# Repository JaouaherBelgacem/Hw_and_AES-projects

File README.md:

******Hw and AES projects TEAM-01 ******

This folder is for Prof Ali Hayek projects of Hardware engineering and Advanced Embedded System's projects

---------Team Members AES---------
* Jaouaher Belgacem
* Jasmeet Singh

---------Team Members HWE---------
* Jaouaher Belgacem
* Jasmeet Singh
* Evrard Leuteu Feukeu

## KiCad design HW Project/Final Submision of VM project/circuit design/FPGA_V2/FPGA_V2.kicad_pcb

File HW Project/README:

************ The Project Submission ************
* The draft submission of the documentation, vhdl and fpga implementations are included in the Vending machine project folder.

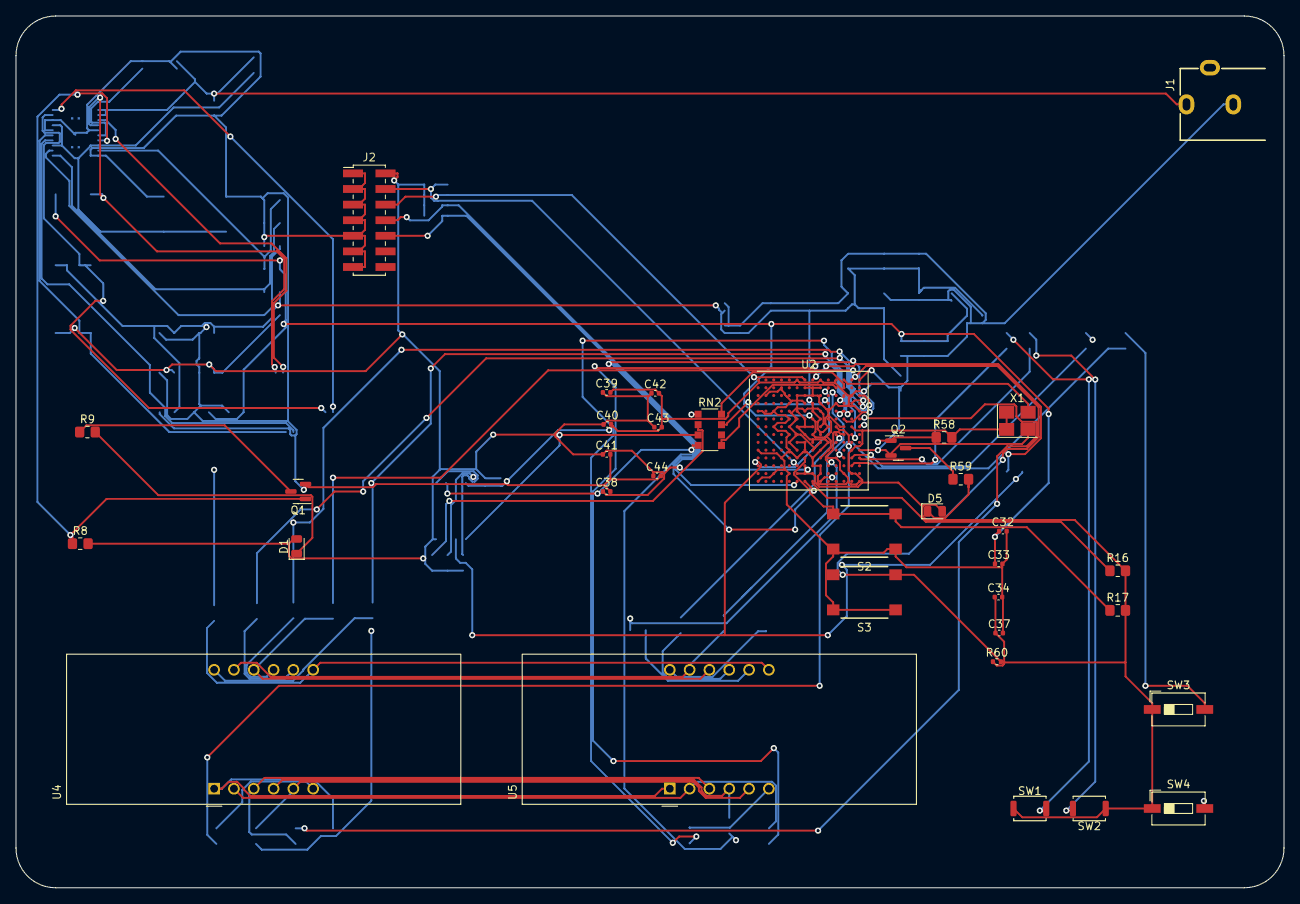
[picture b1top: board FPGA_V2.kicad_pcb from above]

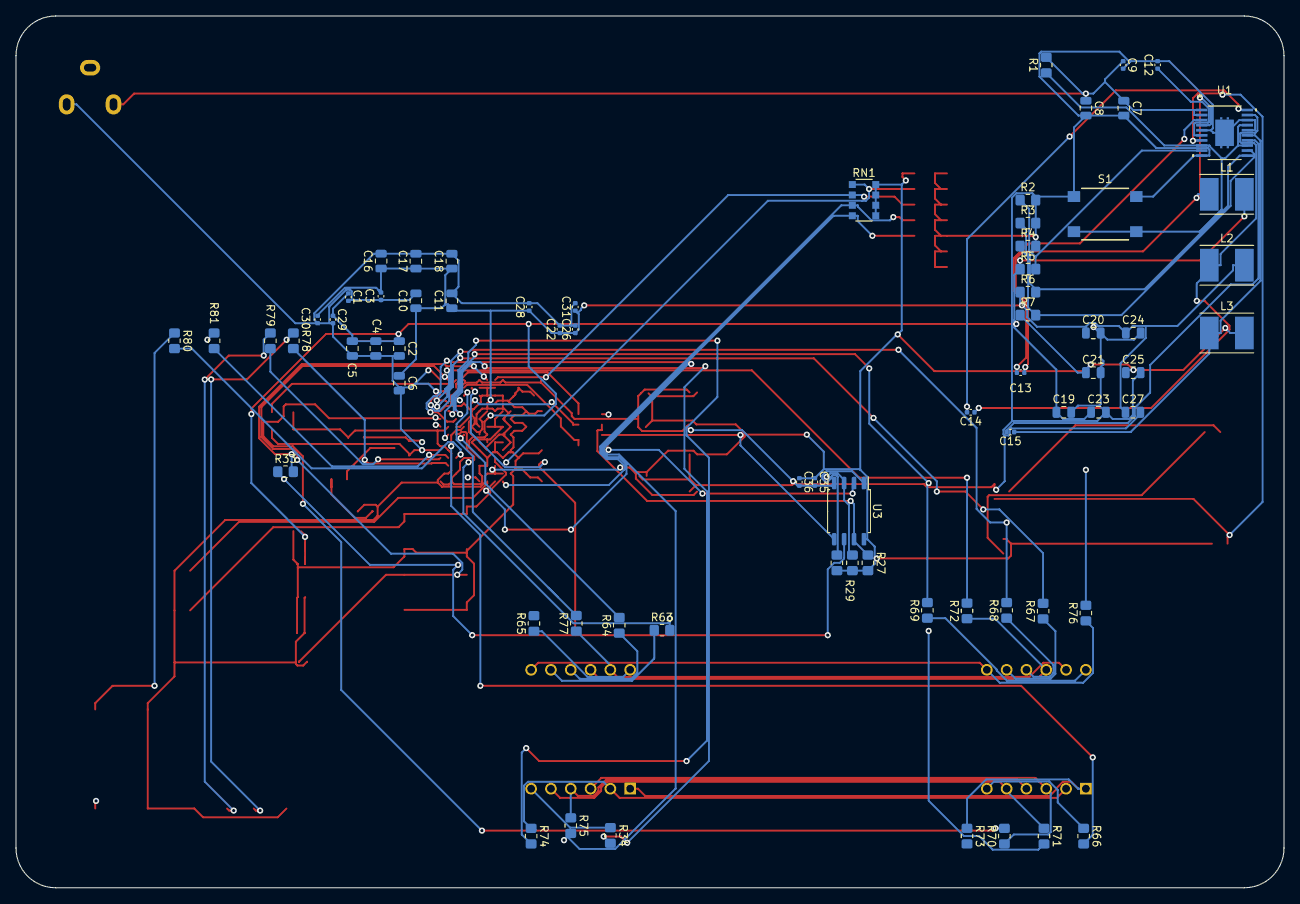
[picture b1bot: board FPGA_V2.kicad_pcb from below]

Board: 2 copper layers, 162.6 x 111.8 mm, 106 parts (71 on the bottom side), 81 nets.

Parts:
C1, C3, C22, C26, C28, C29, C38, C39: 4.7 uF; C_0402_1005Metric
C2, C4, C5, C6, C10, C11, C16, C17, C18: 0.47 uF; C_0805_2012Metric
C7, C8: 10 uF; C_0805_2012Metric
C9, C13, C14, C15, C32, C33, C35, C37: 0.1 uF; C_0402_1005Metric
C12, C36: 1 uF; C_0402_1005Metric
C19, C20, C21, C23, C24, C25, C27: 22 uF; C_0805_2012Metric
C30, C34, C44: 47 uF; C_0402_1005Metric
C31: 100 uF; C_0402_1005Metric
C40, C41, C42, C43: 0.47 uF; C_0402_1005Metric
D1: POWER_GOOD; LED_0805_2012Metric
D5: FPGA_DONE; LED_0805_2012Metric
J1: Barrel_Jack_Switch; PJ_102B
J2: XILINX_JTAG; PinHeader_2x07_P2.00mm_Vertical_SMD
L1, L2, L3: 2.2 uH; L_Taiyo-Yuden_NR-50xx_HandSoldering
Q1, Q2: DMN2020L; SOT-23
R1, R8: 100K; R_0805_2012Metric_Pad1.20x1.40mm_HandSolder
R2, R3, R4: 2.2K; R_0805_2012Metric_Pad1.20x1.40mm_HandSolder
R5: 3.0K; R_0805_2012Metric_Pad1.20x1.40mm_HandSolder
R6, R9, R59: 680; R_0805_2012Metric_Pad1.20x1.40mm_HandSolder
R7: 7.36K; R_0805_2012Metric_Pad1.20x1.40mm_HandSolder
R16, R17, R27, R28, R29: 4.75K; R_0805_2012Metric_Pad1.20x1.40mm_HandSolder
R33: 49.9; R_0805_2012Metric_Pad1.20x1.40mm_HandSolder
R34, R58, R63, R64, R65, R66, R67, R68, R69, R70, R71, R72, R73, R74, R75, R76, R77, R78, R79, R80, R81: 330; R_0805_2012Metric_Pad1.20x1.40mm_HandSolder
R60: 4.75K; R_0402_1005Metric
RN1: 10K; R_Array_Convex_4x1206
RN2: 49.9; R_Array_Convex_4x1206
S1, S2, S3: B3FS_1010P
SW1, SW2: SW_Push; SW_Push_SPST_NO_Alps_SKRK
SW3, SW4: SW_DIP_x01; SW_DIP_SPSTx01_Slide_6.7x4.1mm_W6.73mm_P2.54mm_LowProfile_J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
U1: TPS65581; PWP20_2P4X3P4_TEX
U2: XC7S50-FTGB196; Xilinx_FTGB196
U3: QSPI_Flash_SOIC8; SOIC-8_5.275x5.275mm_P1.27mm
U4, U5: CA56-12CGKWA
X1: DSC61XX; Oscillator_SMD_Abracon_ASE-4Pin_3.2x2.5mm_HandSoldering

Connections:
+1V0: C3.1, C6.1, C10.1, C11.1, C16.1, C17.1, C18.1, C20.1, C22.1, C24.1, C26.1, C27.1, C28.1, C30.1, C31.1, L2.2, R6.1, U2.D6 (VCCINT), U2.D8 (VCCINT), U2.E5 (VCCBRAM), U2.E7 (VCCINT), U2.E9 (VCCINT), U2.F6 (VCCINT), U2.G5 (VCCBRAM), U2.G9 (VCCINT), U2.H6 (VCCINT), U2.J5 (VCCBRAM), U2.J9 (VCCINT), U2.K6 (VCCINT), U2.K8 (VCCINT)
+1V8: C1.1, C2.1, C4.1, C5.1, C19.1, C23.1, C29.1, C32.1, C33.1, L1.2, R5.1, U2.F8 (VCCADC_0), U2.F10 (VCCAUX), U2.H8 (VREFP_0), U2.H10 (VCCAUX), U2.K10 (VCCAUX), U2.L9 (VCCAUX)
+3V3: C21.1, C25.1, C34.1, C35.1, C36.1, C37.1, C38.1, C39.1, C40.1, C41.1, C42.1, C43.1, C44.1, D1.2 (A), D5.2 (A), J2.2 (VREF), L3.2, R7.1, R8.2, R16.2, R17.2, R27.2, R28.2, R29.2, R58.2, R60.1, RN1.5 (R4.2), RN1.6 (R3.2), RN1.7 (R2.2), RN1.8 (R1.2), SW1.1, SW2.1, SW3.1, SW4.1, U2.G13 (VCCO_14), U2.K13 (VCCO_14), U2.M7 (M0_0), U2.N6 (VCCO_0), U2.N7 (CFGBVS_0), U2.N8 (VCCO_0), U2.N13 (VCCO_14), U3.8 (VCC), X1.1 (OE), X1.4 (VCC)
+12V: C7.1, C8.1, C9.1, J1.1, R1.2, U1.1 (VIN), U1.2 (VIN)
/IO/AN0: R69.1, U4.12 (CA1)
/IO/AN1: R68.1, U4.9 (CA2)
/IO/AN2: R67.1, U4.8 (CA3)
/IO/AN3: R66.1, U4.6 (CA4)
/IO/AN4: R65.1, U5.12 (CA1)
/IO/AN5: R64.1, U5.9 (CA2)
/IO/AN6: R63.1, U5.8 (CA3)
/IO/AN7: R34.1, U5.6 (CA4)
/IO/DA: R77.1, U4.11 (a), U5.11 (a)
/IO/DB: R76.1, U4.7 (b), U5.7 (b)
/IO/DC: R75.1, U4.4 (c), U5.4 (c)
/IO/DD: R74.1, U4.2 (d), U5.2 (d)
/IO/DE: R73.1, U4.1 (e), U5.1 (e)
/IO/DF: R72.1, U4.10 (f), U5.10 (f)
/IO/DG: R71.1, U4.5 (g), U5.5 (g)
/IO/DP: R70.1, U4.3 (DPX), U5.3 (DPX)
/IO/PS1: R78.1, SW1.2
/IO/PS2: R79.1, SW2.2
/IO/SPI_CS: R29.1, U2.C10 (IO_L2N_T0_D03_14), U3.1 (~CS)
/IO/SPI_DQ0: RN2.3 (R3.1), U3.5 (DQ0)
/IO/SPI_DQ1: RN2.4 (R4.1), U3.2 (DQ1)
/IO/SPI_DQ2: R28.1, RN2.1 (R1.1), U3.3 (DQ2/~WP)
/IO/SPI_DQ3: R27.1, RN2.2 (R2.1), U3.7 (DQ3/~HOLD)
/IO/SPI_F_DQ0: RN2.6 (R3.2), U2.E11 (IO_0_14)
/IO/SPI_F_DQ1: RN2.5 (R4.2), U2.B11 (IO_L1P_T0_D00_MOSI_14)
/IO/SPI_F_DQ2: RN2.8 (R1.2), U2.B12 (IO_L1N_T0_D01_DIN_14)
/IO/SPI_F_DQ3: RN2.7 (R2.2), U2.D10 (IO_L2P_T0_D02_14)
/IO/SPI_SCLK: R33.1, U2.B10 (IO_L3P_T0_DQS_PUDC_B_14), U3.6 (CLK)
/IO/SW1: R80.1, SW3.2
/IO/SW2: R81.1, SW4.2
/Power/PGOOD: Q1.1 (G), R8.1, U1.7 (PG)
/Power/SW1: C13.1, L1.1, U1.4 (SW1)
/Power/SW2: C14.1, L2.1, U1.19 (SW2)
/Power/SW3: C15.1, L3.1, U1.15 (SW3)
/Utilities/FPGA_DONE: Q2.1 (G), R58.1, U2.P9 (DONE_0)
/Utilities/INIT_B: R16.1, U2.P8 (INIT_B_0)
/Utilities/JTAG_TCK: J2.6 (TCK), RN1.2 (R2.1), U2.A7 (TCK_0)
/Utilities/JTAG_TDI: J2.10 (TDI), RN1.4 (R4.1), U2.P7 (TDI_0)
/Utilities/JTAG_TDO: J2.8 (TDO), RN1.3 (R3.1), U2.P6 (TDO_0)
/Utilities/JTAG_TMS: J2.4 (TMS), RN1.1 (R1.1), U2.M6 (TMS_0)
/Utilities/PROGRAM_B: R17.1, S2.3, S2.4, U2.L7 (PROGRAM_B_0)
GND: C1.2, C2.2, C3.2, C4.2, C5.2, C6.2, C7.2, C8.2, C9.2, C10.2, C11.2, C12.2, C16.2, C17.2, C18.2, C19.2, C20.2, C21.2, C22.2, C23.2, C24.2, C25.2, C26.2, C27.2, C28.2, C29.2, C30.2, C31.2, C32.2, C33.2, C34.2, C35.2, C36.2, C37.2, C38.2, C39.2, C40.2, C41.2, C42.2, C43.2, C44.2, J1.2, J2.1 (GND), J2.3 (GND), J2.5 (GND), J2.7 (GND), J2.9 (GND), J2.11 (GND), J2.13 (GND), Q1.2 (S), Q2.2 (S), R2.2, R3.2, R4.2, S1.1, S1.2, S2.1, S2.2, S3.1, S3.2, U1.5 (PGND1), U1.10 (GND), U1.16 (PGND3), U1.18 (PGND2), U1.21 (PAD), U2.A1 (GND), U2.A6 (GND), U2.A9 (GND), U2.A11 (GND), U2.A14 (GND), U2.B4 (GND), U2.B7 (GND), U2.B8 (VCCBATT_0), U2.B9 (GND), U2.C2 (GND), U2.C6 (GND), U2.C7 (GND), U2.C8 (GND), U2.C9 (GND), U2.C13 (GND), U2.D5 (GND), U2.D7 (GND), U2.D9 (GND), U2.D11 (GND), U2.E1 (GND), U2.E3 (GND), U2.E6 (GND), U2.E8 (GND), U2.E10 (GND), U2.E14 (GND), U2.F5 (GND), U2.F7 (GNDADC_0), U2.F9 (GND), U2.G3 (GND), U2.G6 (GND), U2.G7 (VREFN_0), U2.G8 (VP_0), U2.G10 (GND), U2.G12 (GND), U2.H5 (GND), U2.H7 (VN_0), U2.H9 (GND), U2.J6 (GND), U2.J7 (DXN_0), U2.J8 (DXP_0), U2.J10 (GND), U2.K1 (GND), U2.K5 (GND), U2.K7 (GND), U2.K9 (GND), U2.K14 (GND), U2.L4 (GND), U2.L6 (GND), U2.L8 (GND), U2.L10 (GND), U2.L11 (GND), U2.M8 (M1_0), U2.M9 (M2_0), U2.N3 (GND), U2.N5 (GND), U2.N9 (GND), U2.N12 (GND), U2.P1 (GND), U2.P14 (GND), U3.4 (VSS), X1.2 (GND)
unnamed: D1.1 (K), R9.2
unnamed: D5.1 (K), R59.2
unnamed: Q1.3 (D), R9.1
unnamed: Q2.3 (D), R59.1
unnamed: R1.1, S1.3, S1.4, U1.8 (EN1), U1.13 (EN3), U1.17 (EN2)
unnamed: C13.2, U1.3 (VBST1)
unnamed: C14.2, U1.20 (VBST2)
unnamed: C15.2, U1.14 (VBST3)
unnamed: R2.1, R5.2, U1.9 (VFB1)
unnamed: R3.1, R6.2, U1.11 (VFB2)
unnamed: R4.1, R7.2, U1.12 (VFB3)
unnamed: C12.1, U1.6 (VREG5)
unnamed: R76.2, U2.C12 (IO_L6N_T0_D08_VREF_14)
unnamed: R77.2, U2.C11 (IO_L6P_T0_FCS_B_14)
unnamed: R74.2, U2.E12 (IO_L7N_T1_D10_14)
unnamed: R75.2, U2.F12 (IO_L7P_T1_D09_14)
unnamed: R72.2, U2.D13 (IO_L8N_T1_D12_14)
unnamed: R73.2, U2.D12 (IO_L8P_T1_D11_14)
unnamed: R70.2, U2.F14 (IO_L9N_T1_DQS_D13_14)
unnamed: R71.2, U2.G14 (IO_L9P_T1_DQS_14)
unnamed: R69.2, U2.E13 (IO_L10N_T1_D15_14)
unnamed: R67.2, U2.C14 (IO_L11N_T1_SRCC_14)
unnamed: R68.2, U2.D14 (IO_L11P_T1_SRCC_14)
unnamed: R65.2, U2.F11 (IO_L12N_T1_MRCC_14)
unnamed: R66.2, U2.G11 (IO_L12P_T1_MRCC_14)
unnamed: R63.2, U2.H12 (IO_L13N_T2_MRCC_14)
unnamed: R64.2, U2.H11 (IO_L13P_T2_MRCC_14)
unnamed: R34.2, U2.H13 (IO_L14P_T2_SRCC_14)
unnamed: R79.2, U2.L14 (IO_L15N_T2_DQS_DOUT_CSO_B_14)
unnamed: R78.2, U2.M13 (IO_L15P_T2_DQS_RDWR_B_14)
unnamed: R81.2, U2.L13 (IO_L16N_T2_D31_14)
unnamed: R80.2, U2.L12 (IO_L16P_T2_CSI_B_14)
SPI_F_SCLK: R33.2, U2.A8 (CCLK_0)
SYSCLK: U2.A12 (IO_L4P_T0_D04_14), X1.3 (OUT)
SYSRES: R60.2, S3.3, S3.4, U2.A13 (IO_L4N_T0_D05_14)

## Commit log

2023-05-02 Concept Diagram
2023-06-01 Draft Submission
2023-06-05 edits
2023-06-06 labs
2023-06-09 Create DrinksVendingTb
2023-06-16 submission
2023-06-17 Integration
2023-06-18 Revert "submission"
    This reverts commit 9fa0c6d1e3d3efe90a9751d50ad612d15835e500.
2023-06-18 Revert "submission"
    This reverts commit 5839938e218e5adf689c9d48ac4ea64a1e4b71c5.
2023-06-18 Revert "Update vendingM.vhd.bak"
    This reverts commit 083c5f3751cf6ce0338f16ce263ac84ede2c29dc.
2023-06-18 Revert "Revert "Update vendingM.vhd.bak""
    This reverts commit c1763393c29123be40179117ea98649629e50d0c.
2023-06-18 Revert "Integration"
    This reverts commit 5864f8d8f335edb762fc9f45bd6fac4fffe31788.
2023-06-18 recommit Integration
2023-06-18 edit
2023-06-19 final commit
2023-06-20 Create tb
2023-06-21 Project Work Submit
2023-06-21 Donate to Charity if you dont selct Drink Danke Schone
2023-06-22 Placing Presentation in HW Folder
2023-07-05 final doc
2023-07-10 Document Submission
